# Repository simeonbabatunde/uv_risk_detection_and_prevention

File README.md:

### UV Risk Detection and Alert System

#### Team UV
- Kristopher Kohm
- Simeon Babatunde
- Benjamin Coomes
- Miriam Lozneanu

#### System Description
The UV risk detection and alert system is a set of wearable devices that inform the user about UV exposure rate. One device senses UV radiation and the other displays the UV radiation levels. The display device shows the current and average UV index. The display is in the form of two LED bars that ‘fill up’ as exposure increases, and ‘empty’ as exposure decreases. The sensor device can be clipped onto a hat or backpack. The display device is worn on the user’s wrist. The system lets people know when they have experienced a healthy amount of radiation and when their exposure is approaching dangerous levels.

#### Image(s)

October 3, 2017

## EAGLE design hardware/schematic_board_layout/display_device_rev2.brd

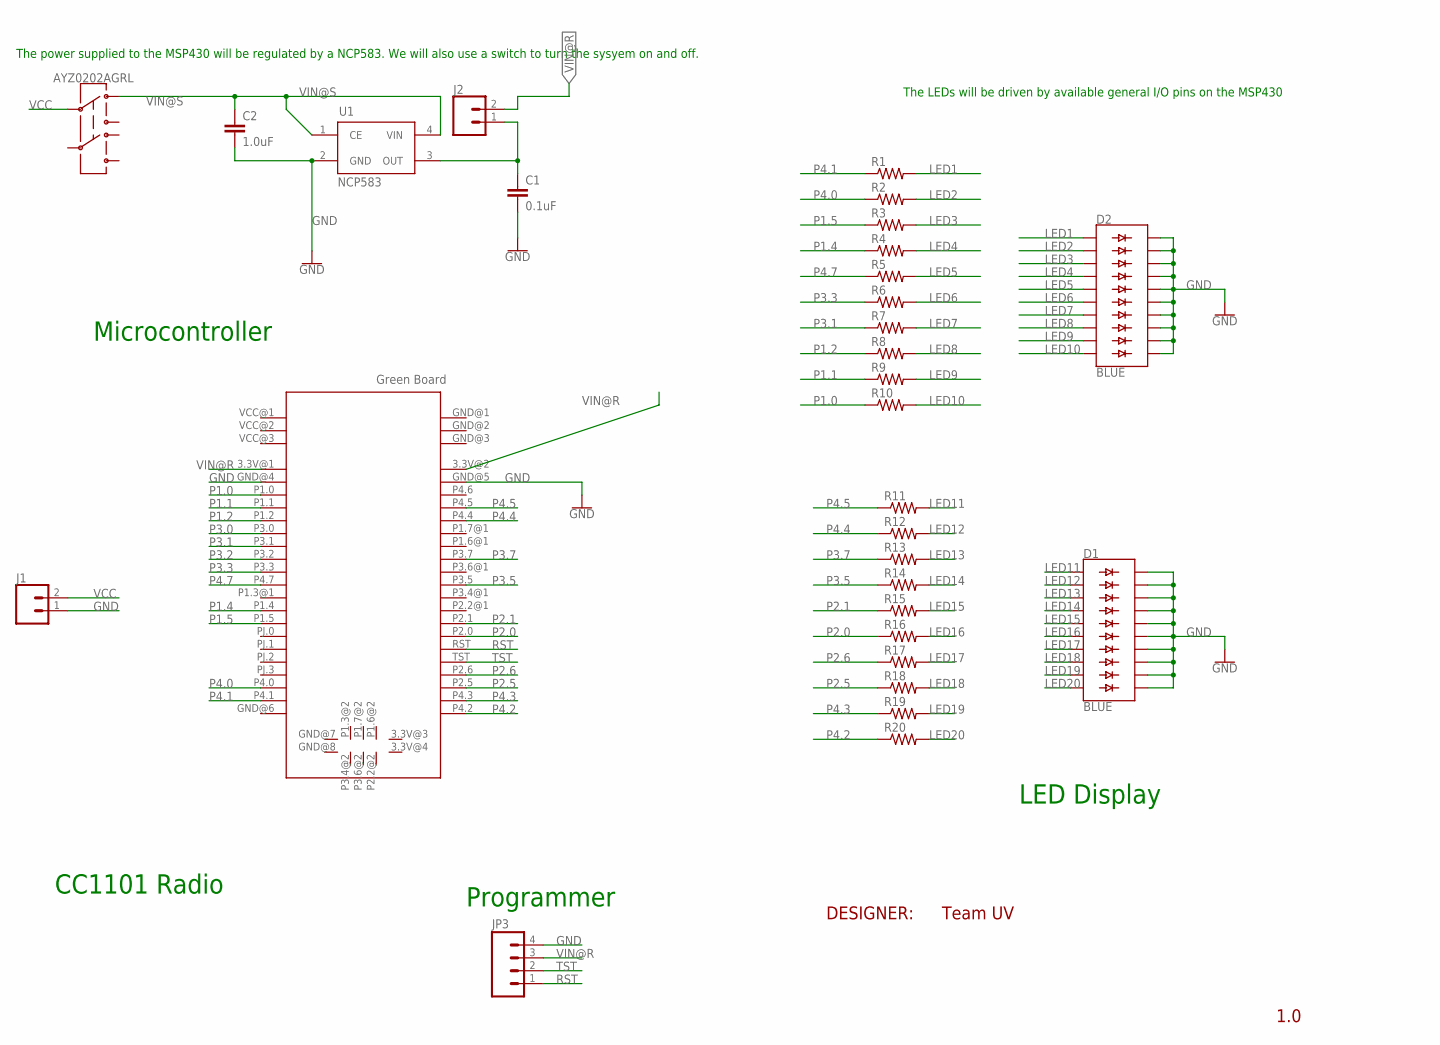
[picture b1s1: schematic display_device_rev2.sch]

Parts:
AYZ0202AGRL: SWITCH-DPDT-SMD-AYZ0202; SWITCH_DPDT_SMD_AYZ0202
C1: 0.1uF; 0805
C2: 1.0uF; 0805
D1, D2: BLUE; LED_BARGRAPH_10
J1, J2: CONN_02; 1X02
JP3: M04PTH; 1X04
R1, R2, R3, R4, R5, R6, R7, R8, R9, R10, R11, R12, R13, R14, R15, R16, R17, R18, R19, R20: R-US_R0805; R0805
U1: NCP583; SC82-AB_1PRIMARY
U$1: GREEDNBRD; GREENBRD

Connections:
GND: C1.2, C2.2, D1.11 (C9), D1.12 (C8), D1.13 (C7), D1.14 (C6), D1.15 (C5), D1.16 (C4), D1.17 (C3), D1.18 (C2), D1.19 (C1), D1.20 (C), D2.11 (C9), D2.12 (C8), D2.13 (C7), D2.14 (C6), D2.15 (C5), D2.16 (C4), D2.17 (C3), D2.18 (C2), D2.19 (C1), D2.20 (C), J1.1, JP3.4, U1.2 (GND), U$1.GND@4 (GND), U$1.GND@5 (GND)
LED1: D2.1 (A), R1.2
LED2: D2.2 (A1), R2.2
LED3: D2.3 (A2), R3.2
LED4: D2.4 (A3), R4.2
LED5: D2.5 (A4), R5.2
LED6: D2.6 (A5), R6.2
LED7: D2.7 (A6), R7.2
LED8: D2.8 (A7), R8.2
LED9: D2.9 (A8), R9.2
LED10: D2.10 (A9), R10.2
LED11: D1.1 (A), R11.2
LED12: D1.2 (A1), R12.2
LED13: D1.3 (A2), R13.2
LED14: D1.4 (A3), R14.2
LED15: D1.5 (A4), R15.2
LED16: D1.6 (A5), R16.2
LED17: D1.7 (A6), R17.2
LED18: D1.8 (A7), R18.2
LED19: D1.9 (A8), R19.2
LED20: D1.10 (A9), R20.2
P1.0: R10.1, U$1.P1.0
P1.1: R9.1, U$1.P1.1
P1.2: R8.1, U$1.P1.2
P1.4: R4.1, U$1.P1.4
P1.5: R3.1, U$1.P1.5
P2.0: R16.1, U$1.P2.0
P2.1: R15.1, U$1.P2.1
P2.5: R18.1, U$1.P2.5
P2.6: R17.1, U$1.P2.6
P3.0: U$1.P3.0
P3.1: R7.1, U$1.P3.1
P3.2: U$1.P3.2
P3.3: R6.1, U$1.P3.3
P3.5: R14.1, U$1.P3.5
P3.7: R13.1, U$1.P3.7
P4.0: R2.1, U$1.P4.0
P4.1: R1.1, U$1.P4.1
P4.2: R20.1, U$1.P4.2
P4.3: R19.1, U$1.P4.3
P4.4: R12.1, U$1.P4.4
P4.5: R11.1, U$1.P4.5
P4.7: R5.1, U$1.P4.7
RST: JP3.1, U$1.RST
TOPIN: C1.1, J2.1, U1.3 (OUT)
TST: JP3.2, U$1.TST
VCC: AYZ0202AGRL.2, J1.2
VIN@R: J2.2, JP3.3, U$1.3.3V@1 (3.3V), U$1.3.3V@2 (3.3V)
VIN@S: AYZ0202AGRL.1, C2.1, U1.1 (CE), U1.4 (VIN)

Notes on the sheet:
The LEDs will be driven by available general I/O pins on the MSP430
The power supplied to the MSP430 will be regulated by a NCP583. We will also use a switch to turn the sysyem on and off.
DESIGNER:
Team UV
1.0
Microcontroller
CC1101 Radio
Programmer
LED Display

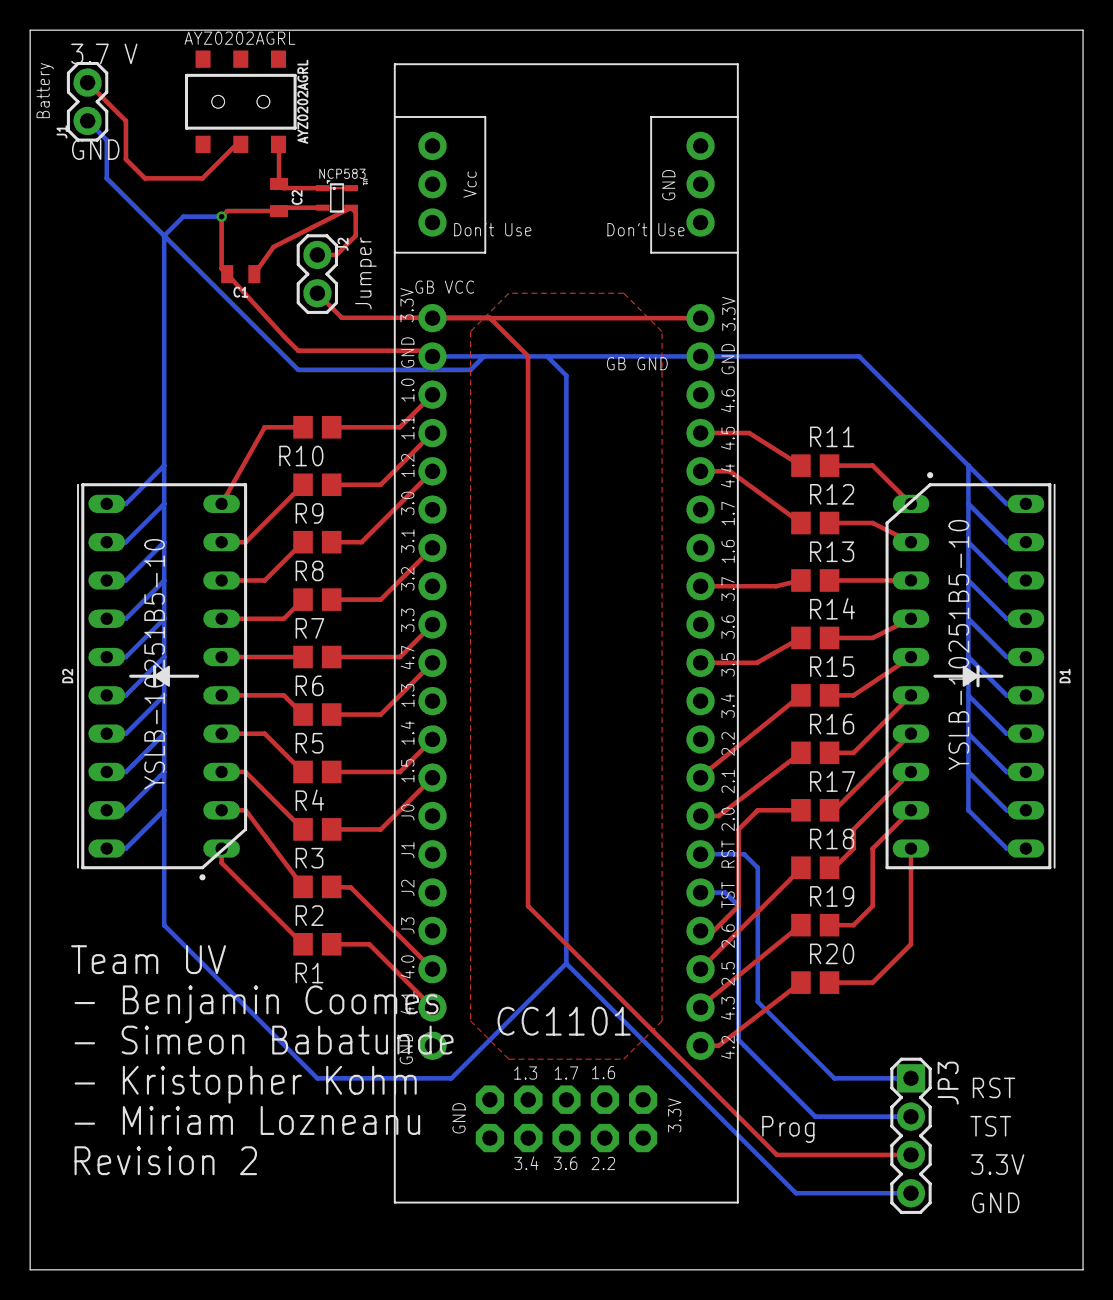
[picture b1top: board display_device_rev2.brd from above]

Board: 2 copper layers, 69.8 x 82.2 mm, 30 parts (0 on the bottom side), 47 nets.

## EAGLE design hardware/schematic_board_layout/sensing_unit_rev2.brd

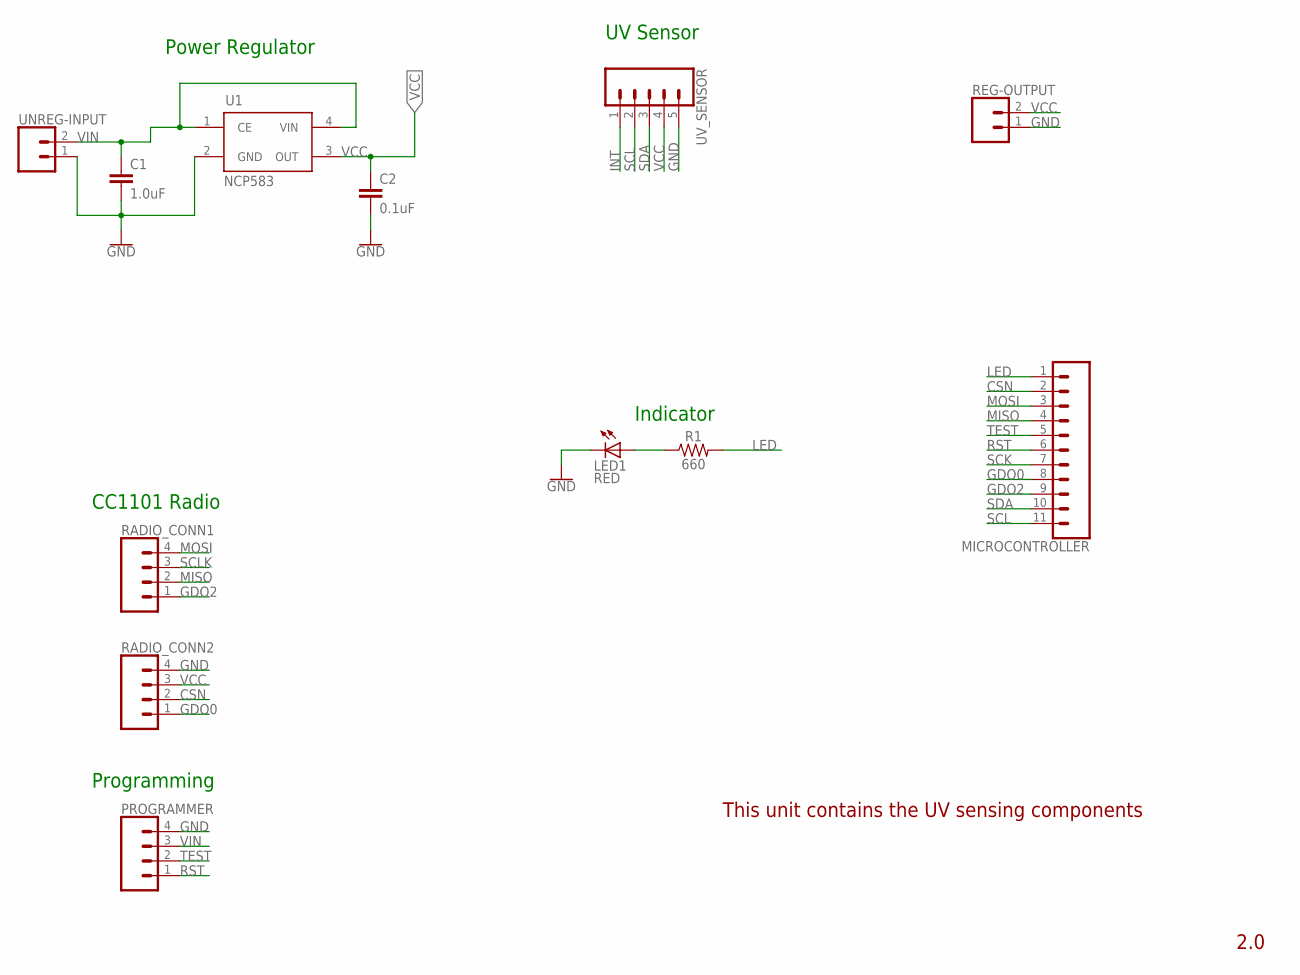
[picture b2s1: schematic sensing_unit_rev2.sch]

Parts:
C1: 1.0uF; 0805
C2: 0.1uF; 0805
LED1: RED; CHIP-LED0805
MICROCONTROLLER: CONN_11; 1X11
PROGRAMMER: CONN_04; 1X04
R1: 660; 0805
RADIO_CONN1, RADIO_CONN2: CONN_04; 1X04
REG-OUTPUT: CONN_02; 1X02
U1: NCP583; SC82-AB_1PRIMARY
UNREG-INPUT: CONN_02; 1X02
UV_SENSOR: CONN_05; 1X05

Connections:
CSN: MICROCONTROLLER.2, RADIO_CONN2.2
GDO0: MICROCONTROLLER.8, RADIO_CONN2.1
GDO2: MICROCONTROLLER.9, RADIO_CONN1.1
GND: C1.2, C2.2, LED1.C, PROGRAMMER.4, RADIO_CONN2.4, REG-OUTPUT.1, U1.2 (GND), UNREG-INPUT.1, UV_SENSOR.5
INT: UV_SENSOR.1
LED: MICROCONTROLLER.1, R1.2
MISO: MICROCONTROLLER.4, RADIO_CONN1.2
MOSI: MICROCONTROLLER.3, RADIO_CONN1.4
unnamed: LED1.A, R1.1
RST: MICROCONTROLLER.6, PROGRAMMER.1
SCK: MICROCONTROLLER.7
SCL: MICROCONTROLLER.11, UV_SENSOR.2
SCLK: RADIO_CONN1.3
SDA: MICROCONTROLLER.10, UV_SENSOR.3
TEST: MICROCONTROLLER.5, PROGRAMMER.2
VCC: C2.1, RADIO_CONN2.3, REG-OUTPUT.2, U1.3 (OUT), UV_SENSOR.4
VIN: C1.1, PROGRAMMER.3, U1.1 (CE), U1.4 (VIN), UNREG-INPUT.2

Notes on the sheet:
2.0
Power Regulator
UV Sensor
Indicator
CC1101 Radio
Programming
This unit contains the UV sensing components

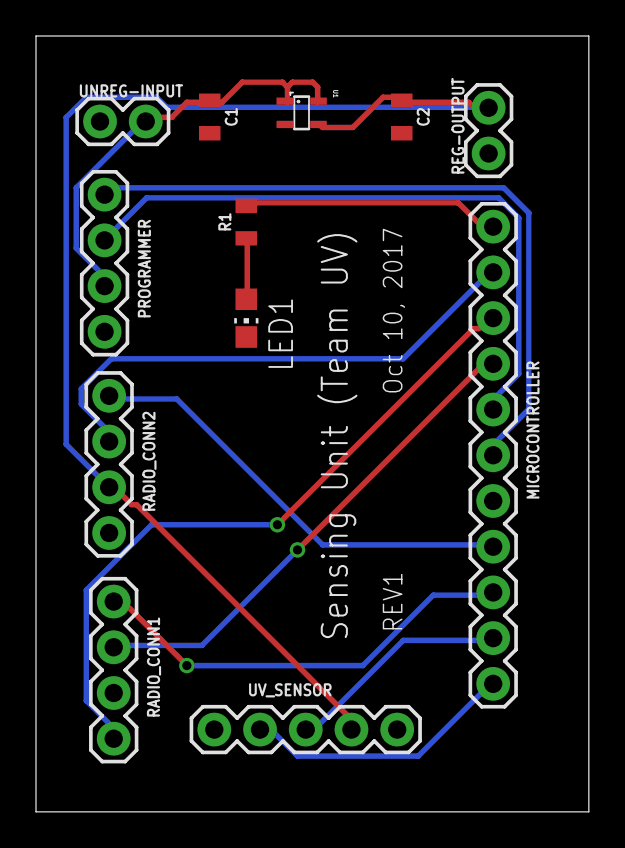
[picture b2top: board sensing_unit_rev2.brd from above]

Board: 2 copper layers, 30.7 x 43.1 mm, 12 parts (0 on the bottom side), 14 nets.

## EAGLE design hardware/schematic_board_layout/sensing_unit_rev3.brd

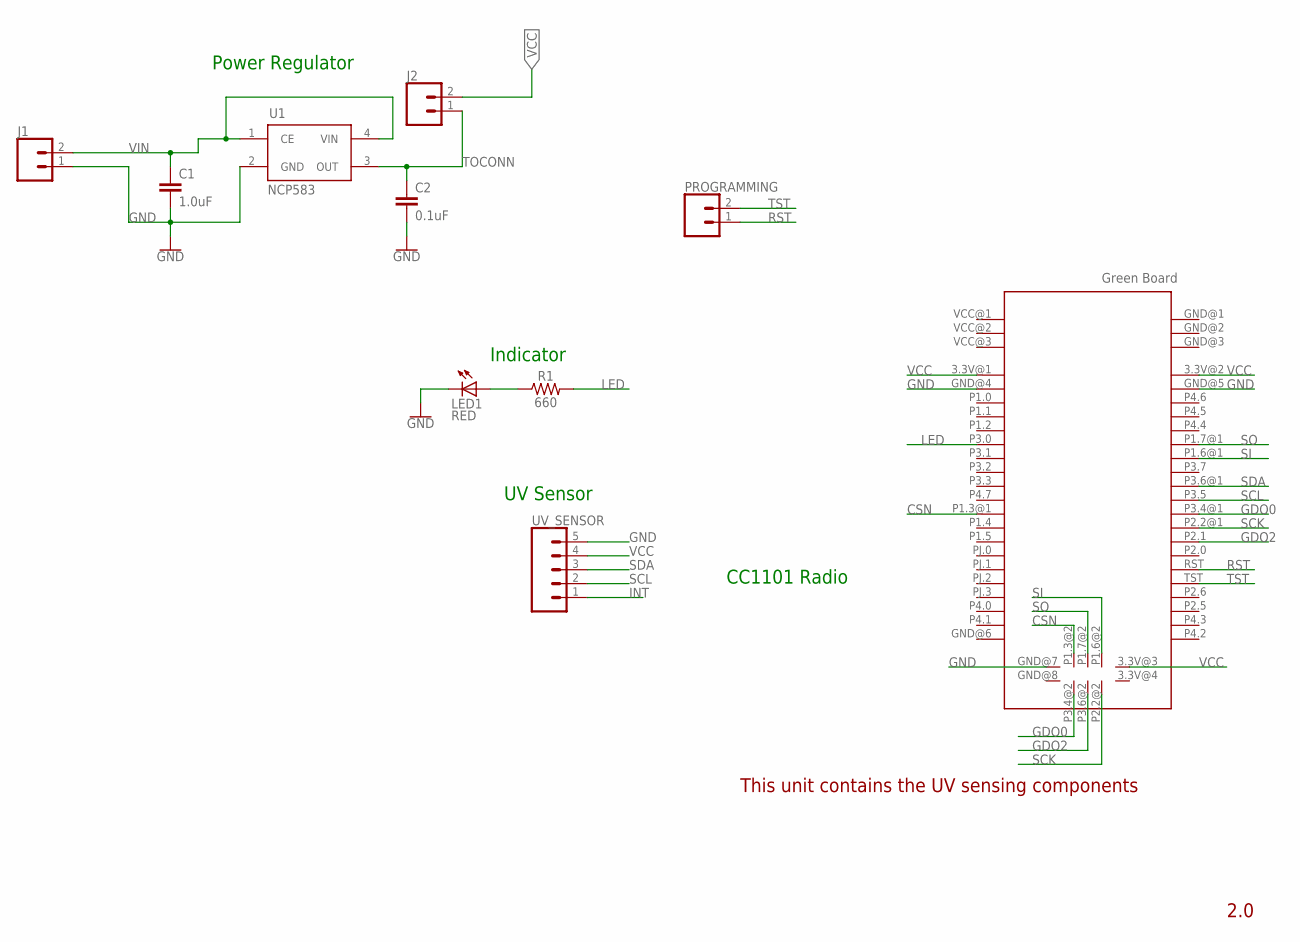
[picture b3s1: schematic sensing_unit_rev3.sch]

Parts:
C1: 1.0uF; 0805
C2: 0.1uF; 0805
J1, J2: CONN_02; 1X02
LED1: RED; CHIP-LED0805
PROGRAMMING: CONN_02; 1X02
R1: 660; 0805
U1: NCP583; SC82-AB_1PRIMARY
U$1: GREEDNBRD; GREENBRD
UV_SENSOR: CONN_05; 1X05

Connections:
CSN: U$1.P1.3@1 (P1.3), U$1.P1.3@2 (P1.3)
GDO0: U$1.P3.4@1 (P3.4), U$1.P3.4@2 (P3.4)
GDO2: U$1.P2.1, U$1.P3.6@2 (P3.6)
GND: C1.2, C2.2, J1.1, LED1.C, U1.2 (GND), U$1.GND@4 (GND), U$1.GND@5 (GND), U$1.GND@7 (GND), UV_SENSOR.5
INT: UV_SENSOR.1
LED: R1.2, U$1.P3.0
unnamed: LED1.A, R1.1
RST: PROGRAMMING.1, U$1.RST
SCK: U$1.P2.2@1 (P2.2), U$1.P2.2@2 (P2.2)
SCL: U$1.P3.5, UV_SENSOR.2
SDA: U$1.P3.6@1 (P3.6), UV_SENSOR.3
SI: U$1.P1.6@1 (P1.6), U$1.P1.6@2 (P1.6)
SO: U$1.P1.7@1 (P1.7), U$1.P1.7@2 (P1.7)
TOCONN: C2.1, J2.1, U1.3 (OUT)
TST: PROGRAMMING.2, U$1.TST
VCC: J2.2, U$1.3.3V@1 (3.3V), U$1.3.3V@2 (3.3V), U$1.3.3V@3 (3.3V), UV_SENSOR.4
VIN: C1.1, J1.2, U1.1 (CE), U1.4 (VIN)

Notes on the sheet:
2.0
Power Regulator
UV Sensor
Indicator
CC1101 Radio
This unit contains the UV sensing components

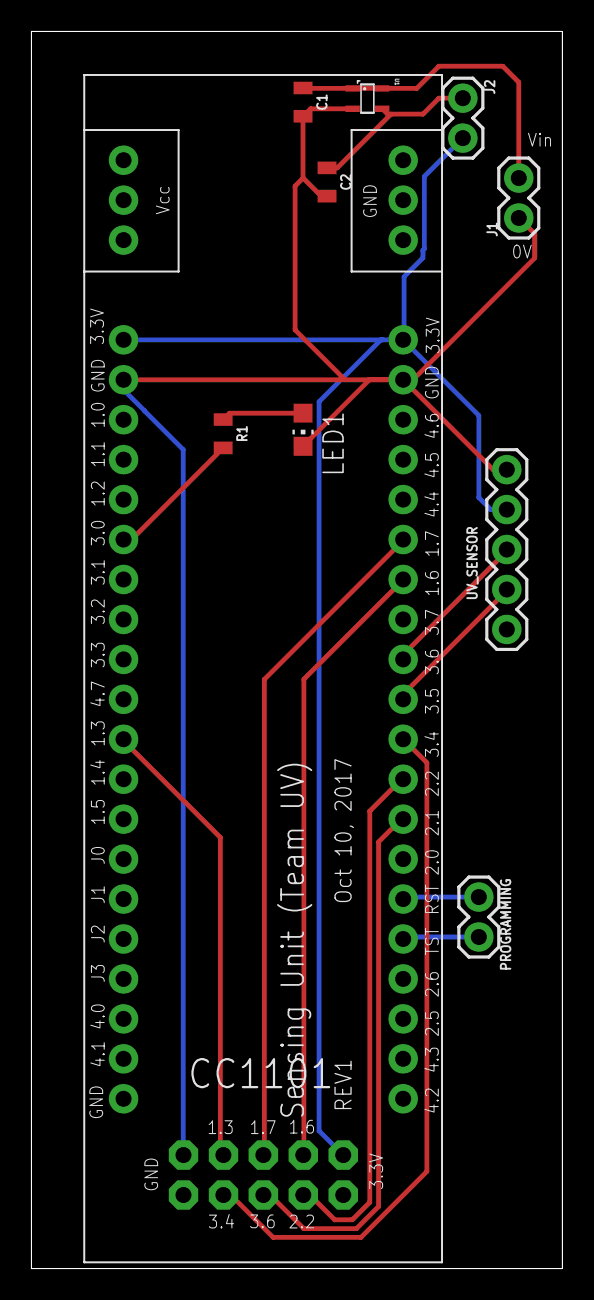
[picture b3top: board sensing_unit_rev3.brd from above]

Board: 2 copper layers, 33.8 x 78.7 mm, 10 parts (0 on the bottom side), 16 nets.

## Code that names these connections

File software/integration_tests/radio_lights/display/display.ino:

#include <cc1101.h>
#include <macros.h>
#include <pins.h>
#include <registers.h>

#include "LedBar.h"
#include "display_unit.h"

#define LED1 P4_2
#define LED2 P2_6
#define LED3 P2_5
#define LED4 P4_3
#define LED5 P2_4
#define LED6 P3_5
#define LED7 P1_2
#define LED8 P3_0
#define LED9 P1_5
#define LED10 P1_4

// Radio receiver setup
byte RX_buffer[2]={0};
byte sizerx;

// Led bar setup
int leds[] = {LED1, LED2, LED3, LED4, LED5, LED6, LED7, LED8, LED9, LED10};
int ledCount = 10;
LedBar ledBar(leds, ledCount);

// display unit setup
Display_Unit du;

void setup()
{
  Serial.begin(9600);
  delay(1000);
  setupRadioReceiver();
}

void loop()
{
   if(Radio.CheckReceiveFlag())
  {
    sizerx=Radio.ReceiveData(RX_buffer);
    Serial.print("Received:[");
    Serial.print(RX_buffer[0],DEC);
    Serial.print(",");
    Serial.print(RX_buffer[1],DEC);
    Serial.println("]");
    Radio.RxOn();
  }

  int led = du.byteToLight(RX_buffer[0]);
  ledBar.lightSingle(led);
}

void setupRadioReceiver(){
  Radio.Init();
  Radio.SetDataRate(4);
  Radio.SetLogicalChannel(1);
  Radio.RxOn();
}

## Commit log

2018-01-07 Created a new repo for the project
2018-01-07 Updated the ReadMe
2018-01-07 Added Image to readMe
2018-01-07 Added other documents

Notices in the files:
parts and their libraries:
SparkFun-Switches: Licensing: Creative Commons ShareAlike 4.0 International - https://creativecommons.org/licenses/by-sa/4.0
